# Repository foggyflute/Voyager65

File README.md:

# V65LE
Low-cost 65% keyboard PCB

[Supported Layouts](http://www.keyboard-layout-editor.com/#/gists/98784f0271c0b4e29edec77185eb883a)

## Features
* Atxmega32a4u controller for Keyplus firmware usage
* Overcurrent and ESD protection, along with physically durable design
* Type-C USB connector
* Easy programming via TC2030-IDC header
* Alps and MX compatibility
* **Completely** open-source: All the files you need to make a keyboard with it, design a case/plate for it, or even produce a batch of PCBs for your next GB, are all to be available free.
* Low-cost with LED circuitry removed. Recommended for Alps-only boards.

## Status
* Main Voyager65 switch matrix confirmed functional.
	* V65AE shares its matrix circuitry and pinout with Voyager65.
* Prototypes yet to be created.

## Variants
* [Voyager65](https://github.com/ai03-2725/Voyager65): The main variant of the Voyager65 family. All the cutting edge features.
* V65LE: This branch. Low-cost variant.
* [V65AE](https://github.com/ai03-2725/Voyager65/tree/V65AE): Alps-specific variant.

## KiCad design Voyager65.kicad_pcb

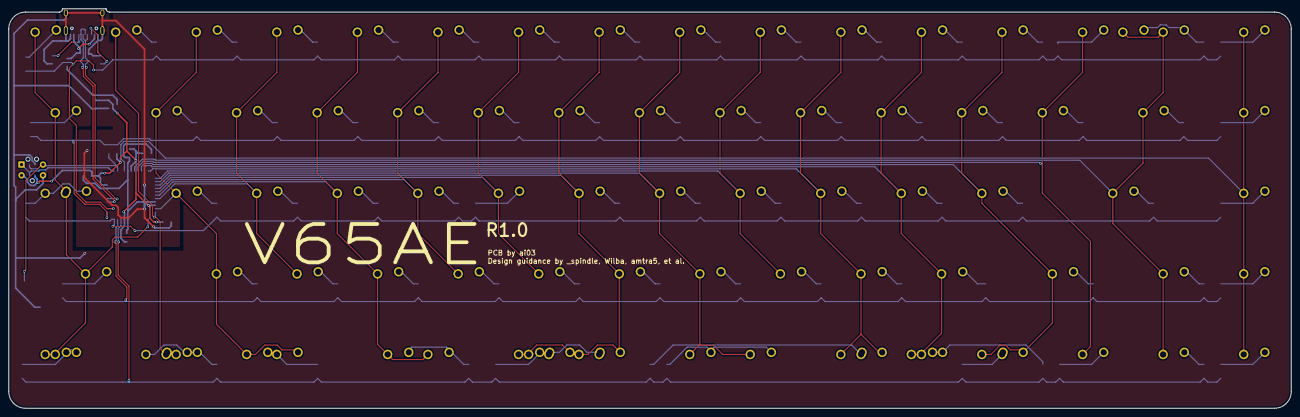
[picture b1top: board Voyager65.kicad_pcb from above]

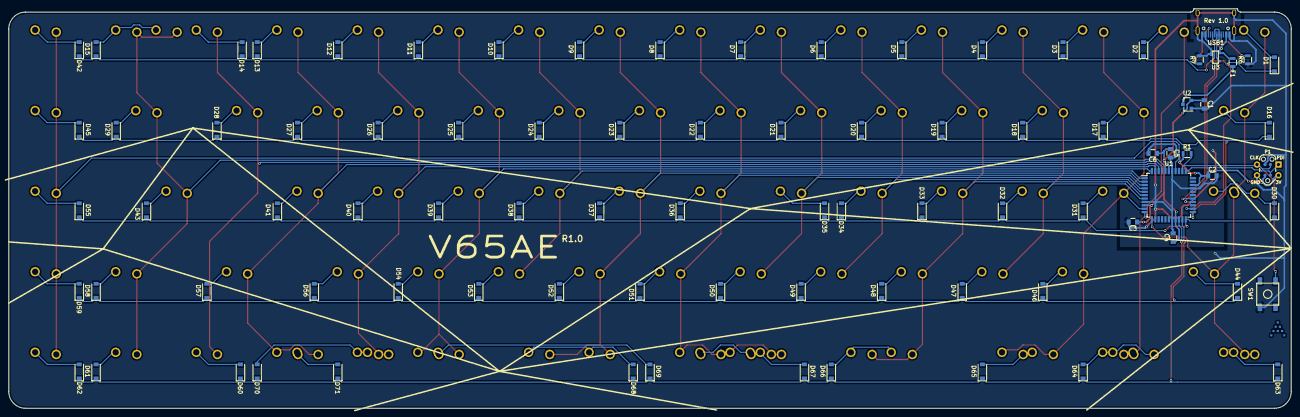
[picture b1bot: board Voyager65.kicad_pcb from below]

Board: 2 copper layers, 303.2 x 94.5 mm, 173 parts (87 on the bottom side), 102 nets.

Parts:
C1: 1u; C_0805
C2, C3, C4, C5: 0.1u; C_0805
C6: 10u; C_0805
D1, D2, D3, D4, D5, D6, D7, D8, D9, D10, D11, D12, D13, D14, D15, D16, D17, D18, D19, D20, D21, D22, D23, D24, D25, D26, D27, D28, D29, D30, D31, D32, D33, D34, D35, D36, D37, D38, D39, D40, D41, D42, D43, D44, D45, D46, D47, D48, D49, D50, D51, D52, D53, D54, D55, D56, D57, D58, D59, D60, D61, D62, D63, D64, D65, D66, D67, D68, D69, D70, D71: D_Small; D_SOD-123
F1: 500mA; R_0805
K_#0_1, K_#1, K_#2, K_#3, K_#4, K_#5, K_#6, K_#7, K_#8, K_#9: MX-1U; ALPS-1U
K_'1: MX-1U; ALPS-1U
K_,1: MX-1U; ALPS-1U
K_-1: MX-1U; ALPS-1U
K_.1: MX-1U; ALPS-1U
K_/1: MX-1U; ALPS-1U
K_;1: MX-1U; ALPS-1U
K_=1: MX-1U; ALPS-1U
K_A1: MX-1U; ALPS-1U
K_B1: MX-1U; ALPS-1U
K_BACK1: MX-2U; ALPS-2U
K_BACK2: MX-1U; ALPS-1U
K_C1: MX-1U; ALPS-1U
K_CAPS1: MX-1.75U; ALPS-1.75U
K_CAPS2: MX-1.25U; ALPS-1.25U
K_D1: MX-1U; ALPS-1U
K_DEL1: MX-1U; ALPS-1U
K_DOWN1: MX-1U; ALPS-1U
K_E1: MX-1U; ALPS-1U
K_ENTER1: MX-2.25U; ALPS-2.25U
K_ESC1: MX-1U; ALPS-1U
K_EX1, K_EX2, K_EX3, K_EX4: MX-1U; ALPS-1U
K_F1: MX-1U; ALPS-1U
K_G1: MX-1U; ALPS-1U
K_H1: MX-1U; ALPS-1U
K_I1: MX-1U; ALPS-1U
K_J1: MX-1U; ALPS-1U
K_K1: MX-1U; ALPS-1U
K_L1: MX-1U; ALPS-1U
K_LEFT1: MX-1U; ALPS-1U
K_LM1, K_LM3, K_LM7: MX-1.5U; ALPS-1.5U
K_LM2, K_LM4, K_LM5, K_LM6: MX-1.25U; ALPS-1.25U
K_M1: MX-1U; ALPS-1U
K_N1: MX-1U; ALPS-1U
K_O1: MX-1U; ALPS-1U
K_P1: MX-1U; ALPS-1U
K_Q1: MX-1U; ALPS-1U
K_R1: MX-1U; ALPS-1U
K_RIGHT1: MX-1U; ALPS-1U
K_RM1, K_RM4, K_RM6: MX-1U; ALPS-1U
K_RM2, K_RM5: MX-1.5U; ALPS-1.5U
K_RM3: MX-1.25U; ALPS-1.25U
K_S1: MX-1U; ALPS-1U
K_SHIFT1: MX-2.25U; ALPS-2.25U
K_SHIFT2: MX-1.75U; ALPS-1.75U
K_T1: MX-1U; ALPS-1U
K_TAB1: MX-1.5U; ALPS-1.5U
K_U1: MX-1U; ALPS-1U
K_UP1: MX-1U; ALPS-1U
K_V1: MX-1U; ALPS-1U
K_W1: MX-1U; ALPS-1U
K_X1: MX-1U; ALPS-1U
K_Y1: MX-1U; ALPS-1U
K_Z1: MX-1U; ALPS-1U
K_[1: MX-1U; ALPS-1U
K_\1: MX-1.5U; ALPS-1.5U
K_]1: MX-1U; ALPS-1U
P1: TC2030-IDC; TC2030-NL_SMALL_AND_IDC_PDI
R1: 10k; R_0805
R6, R7: 5.1k; R_0805
SP1, SP7: MX-2.25U; ALPS-2.25U
SP2: MX-7U; ALPS-1U
SP3: MX-6.25U; ALPS-1U
SP4: MX-1.25U; ALPS-1.25U
SP5, SP9: MX-2.75U; ALPS-2.75U
SP6: MX-6.5U; ALPS-6.5U
SP8: MX-1.5U; ALPS-1.5U
SW1: SW_PUSH; SKQG-1155865
U1: ATXMEGA32A4U-AU; TQFP-44_10x10mm_Pitch0.8mm
U2: MCP1700T-3002E/TT; SOT-23
U3: PRTR5V0U2X; SOT143B
USB1: HRO-TYPE-C-31-M-12

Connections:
+3V3: C1.1, C2.1, C3.1, C4.1, C5.1, C6.1, P1.2, R1.1, U1.9, U1.19, U1.31, U1.39, U2.2
+5V: F1.1, U2.3
COL0: K_CAPS1.1, K_CAPS2.2, K_ESC1.1, K_LM1.1, K_LM2.1, K_SHIFT1.1, K_TAB1.1, U1.12
COL1: K_#1.1, K_LM3.1, K_LM4.2, K_LM5.1, U1.11
COL2: K_#2.1, K_A1.1, K_LM6.1, K_LM7.2, K_Q1.1, K_Z1.1, U1.10
COL3: K_#3.1, K_S1.1, K_W1.1, K_X1.1, U1.7
COL4: K_#4.1, K_C1.1, K_D1.1, K_E1.1, SP1.1, SP7.1, U1.6
COL5: K_#5.1, K_F1.1, K_R1.1, K_V1.1, U1.5
COL6: K_#6.1, K_B1.1, K_G1.1, K_T1.1, U1.4
COL7: K_#7.1, K_H1.1, K_N1.1, K_Y1.1, SP2.1, SP3.2, SP4.1, SP6.2, SP8.1, U1.3
COL8: K_#8.1, K_J1.1, K_M1.1, K_U1.1, SP5.1, SP9.1, U1.2
COL9: K_#9.1, K_,1.1, K_I1.1, K_K1.1, U1.1
COL10: K_#0_1.1, K_.1.1, K_L1.1, K_O1.1, K_RM1.1, K_RM2.2, U1.44
COL11: K_-1.1, K_/1.1, K_;1.1, K_P1.1, K_RM3.1, K_RM4.1, U1.43
COL12: K_'1.1, K_=1.1, K_RM5.1, K_RM6.2, K_SHIFT2.1, K_[1.1, U1.42
COL13: K_DEL1.1, K_LEFT1.1, K_]1.1, U1.41
COL14: K_BACK1.1, K_BACK2.1, K_DOWN1.1, K_ENTER1.1, K_UP1.1, K_\1.1, U1.40
COL15: K_EX1.1, K_EX2.1, K_EX3.1, K_EX4.1, K_RIGHT1.1, U1.37
D+: U1.27, U3.2, USB1.6, USB1.8
D-: U1.26, U3.3, USB1.5, USB1.7
GND: C1.2, C2.2, C3.2, C4.2, C5.2, C6.2, P1.6, R6.1, R7.2, SW1.1, U1.8, U1.18, U1.30, U1.38, U2.1, U3.1, USB1.1, USB1.12, USB1.13
unnamed: D1.2, K_ESC1.2
unnamed: D2.2, K_#1.2
unnamed: D3.2, K_#2.2
unnamed: D4.2, K_#3.2
unnamed: D5.2, K_#4.2
unnamed: D6.2, K_#5.2
unnamed: D7.2, K_#6.2
unnamed: D8.2, K_#7.2
unnamed: D9.2, K_#8.2
unnamed: D10.2, K_#9.2
unnamed: D11.2, K_#0_1.2
unnamed: D12.2, K_-1.2
unnamed: D13.2, K_=1.2
unnamed: D14.2, K_DEL1.2
unnamed: D15.2, K_BACK1.2, K_BACK2.2
unnamed: D16.2, K_TAB1.2
unnamed: D17.2, K_Q1.2
unnamed: D18.2, K_W1.2
unnamed: D19.2, K_E1.2
unnamed: D20.2, K_R1.2
unnamed: D21.2, K_T1.2
unnamed: D22.2, K_Y1.2
unnamed: D23.2, K_U1.2
unnamed: D24.2, K_I1.2
unnamed: D25.2, K_O1.2
unnamed: D26.2, K_P1.2
unnamed: D27.2, K_[1.2
unnamed: D28.2, K_]1.2
unnamed: D29.2, K_\1.2
unnamed: D30.2, K_CAPS1.2, K_CAPS2.1
unnamed: D31.2, K_A1.2
unnamed: D32.2, K_S1.2
unnamed: D33.2, K_D1.2
unnamed: D34.2, K_F1.2
unnamed: D35.2, K_G1.2
unnamed: D36.2, K_H1.2
unnamed: D37.2, K_J1.2
unnamed: D38.2, K_K1.2
unnamed: D39.2, K_L1.2
unnamed: D40.2, K_;1.2
unnamed: D41.2, K_'1.2
unnamed: D42.2, K_EX1.2
unnamed: D43.2, K_ENTER1.2
unnamed: D44.2, K_SHIFT1.2
unnamed: D45.2, K_EX2.2
unnamed: D46.2, K_Z1.2
unnamed: D47.2, K_X1.2
unnamed: D48.2, K_C1.2
unnamed: D49.2, K_V1.2
unnamed: D50.2, K_B1.2
unnamed: D51.2, K_N1.2
unnamed: D52.2, K_M1.2
unnamed: D53.2, K_,1.2
unnamed: D54.2, K_.1.2
unnamed: D55.2, K_EX3.2
unnamed: D56.2, K_/1.2
unnamed: D57.2, K_SHIFT2.2
unnamed: D58.2, K_UP1.2
unnamed: D59.2, K_EX4.2
unnamed: D60.2, K_LEFT1.2
unnamed: D61.2, K_DOWN1.2
unnamed: D62.2, K_RIGHT1.2
unnamed: D63.2, K_LM1.2, K_LM2.2
unnamed: D64.2, K_LM3.2, K_LM4.1, K_LM5.2
unnamed: D65.2, K_LM6.2, K_LM7.1
unnamed: D66.2, SP1.2, SP7.2
unnamed: D67.2, SP2.2, SP3.1, SP4.2, SP6.1, SP8.2
unnamed: D68.2, SP5.2, SP9.2
unnamed: D69.2, K_RM1.2, K_RM2.1
unnamed: D70.2, K_RM3.2, K_RM4.2
unnamed: D71.2, K_RM5.2, K_RM6.1
unnamed: R6.2, USB1.4
unnamed: R7.1, USB1.10
PDI: P1.1, U1.34
PDI_CLK: P1.5, R1.2, SW1.2, U1.35
ROW0: D1.1, D2.1, D3.1, D4.1, D5.1, D6.1, D7.1, D8.1, D9.1, D10.1, D11.1, D12.1, D13.1, D14.1, D15.1, D42.1, U1.24
ROW1: D16.1, D17.1, D18.1, D19.1, D20.1, D21.1, D22.1, D23.1, D24.1, D25.1, D26.1, D27.1, D28.1, D29.1, D45.1, U1.23
ROW2: D30.1, D31.1, D32.1, D33.1, D34.1, D35.1, D36.1, D37.1, D38.1, D39.1, D40.1, D41.1, D43.1, D55.1, U1.22
ROW3: D44.1, D46.1, D47.1, D48.1, D49.1, D50.1, D51.1, D52.1, D53.1, D54.1, D56.1, D57.1, D58.1, D59.1, U1.21
ROW4: D60.1, D61.1, D62.1, D63.1, D64.1, D65.1, D66.1, D67.1, D68.1, D69.1, D70.1, D71.1, U1.20
VCC: F1.2, U3.4, USB1.2, USB1.11

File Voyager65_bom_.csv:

Component,Description,Part,References,Value,Footprint,Quantity Per PCB,Datasheet
1,Unpolarized capacitor,C_Small,C2 C3 C4 C5,0.1u,C_0603,4,
2,Unpolarized capacitor,C_Small,C6,10u,C_0603,1,
3,Unpolarized capacitor,C_Small,C1,1u,C_0603,1,
4,"Diode, small symbol",D_Small,D1 D2 D3 D4 D5 D6 D7 D8 D9 D10 D11 D12 D13 D14 D15 D16 D17 D18 D19 D20 D21 D22 D23 D24 D25 D26 D27 D28 D29 D30 D31 D32 D33 D34 D35 D36 D37 D38 D39 D40 D41 D42 D43 D44 D45 D46 D47 D48 D49 D50 D51 D52 D53 D54 D55 D56 D57 D58 D59 D60 D61 D62 D63 D64 D65 D66 D67 D68 D69 D70 D71,D_Small,D_SOD-123,71,
5,"resettable fuse, polymeric positive temperature coefficient (PPTC), small symbol",Polyfuse_Small,F1,500mA,R_0805,1,
6,,TC2030-IDC,P1,TC2030-IDC,TC2030-NL_SMALL_AND_IDC_PDI,1,
7,"Resistor, small symbol",R_Small,R1,10k,R_0603,1,
8,"Resistor, small symbol",R_Small,R6 R7,5.1k,R_0603,2,
9,,SW_PUSH,SW1,SW_PUSH,SKQG-1155865,1,
10,"TQFP44, 16k Flash, 4k Boot, 2k SRAM, 1k EEPROM, JTAG, USB",ATXMEGA32A4U-AU,U1,ATXMEGA32A4U-AU,TQFP-44_10x10mm_Pitch0.8mm,1,http://www.atmel.com/Images/Atmel-8387-8-and16-bit-AVR-Micro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
11,"250mA Low Quiscent Current LDO, 3.0V output, SOT-23",MCP1700-3002E_SOT23,U2,MCP1700T-3002E/TT,SOT-23,1,http://ww1.microchip.com/downloads/en/DeviceDoc/20001826C.pdf
12,,PRTR5V0U2X,U3,PRTR5V0U2X,SOT143B,1,
13,,HRO-TYPE-C-31-M-12,USB1,HRO-TYPE-C-31-M-12,HRO-TYPE-C-31-M-12,1,https://datasheet.lcsc.com/szlcsc/TYPE-C-31-M-12-Female-head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





Component Groups:,13
Component Count:,87
Fitted Components:,87
Number of PCBs:,1
Total components:,87
Schematic Version:,
Schematic Date:,
BoM Date:,6/8/2018 1:08:43 AM
Schematic Source:,C:/Users/Ryota/Documents/GitHub/Voyager65/Voyager65.sch
KiCad Version:,Eeschema 4.0.7

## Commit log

2018-01-19 :lollipop: Added .gitattributes & .gitignore files
2018-01-19 Add submodules
2018-01-19 Generate project
2018-01-19 Remove submodule
2018-01-19 Add missing submodule
2018-01-19 Begin building schematic, bit by bit
2018-01-19 Voltage tests
2018-01-19 Continue schematic
2018-01-19 Add libs
2018-01-20 Tune up controller to final state
2018-01-20 Implement ESD protection
2018-01-20 Bind controller footprints
2018-01-20 Generate preliminary netlist
2018-01-20 Change PCB sheet size
2018-01-20 Place 60% footprint
2018-01-20 Sort parts on PCB
2018-01-20 Roughly break out controller
2018-01-21 Place down some matrix stuff
2018-01-21 Create IS31FL3731-SALS2 schem module
2018-01-21 Wire the LED controller
2018-01-21 Add LED matrix labels
2018-01-21 Label row 1 of switches
2018-01-21 Continue labeling and adding keys on matrix
2018-01-22 Build right shift in separate sheet
2018-01-22 Break matrix up into multiple sheets
2018-01-22 Finish labeling key names
2018-01-22 Assign footprints, along with placeholders for mx
2018-01-22 Repair footprints on main matrix sheet
2018-01-22 Repair all mx footprints
2018-01-22 Start placing some footprints
2018-01-22 Fix backspace, finish row 1
2018-01-22 Dislodge PTC for routing
2018-01-22 Place some modifiers
2018-01-22 Layout broken out bottom row
2018-01-22 Fix right shift sizes
2018-01-22 Combine and place right shift cluster
2018-01-22 Combine and position bottom row
2018-01-22 Swap alps row for alps-only fp
2018-01-22 Layout 2nd row
2018-01-22 Layout all keys
2018-01-22 Fix USB net name
2018-01-22 Route USB
2018-01-22 Unroute USB
2018-01-22 Break out controller a bit
2018-01-22 Breakout controller further
2018-01-22 Update breakout for RGB placement
2018-01-22 Remove alps row
2018-01-22 Repair bottom row after refractor]
2018-01-22 Recombine bottom row
2018-01-22 Add RGB
2018-01-22 Position RGBs
2018-01-22 Fix LED MCU breakout
2018-01-22 Wire PDI header
2018-01-22 Rename I2C net for easier routing
2018-01-22 I2C routing
2018-01-22 Preliminary MCU routing
2018-01-22 Wire cols 0-5
2018-01-22 Close for tonight
2018-01-23 Route bus upwards
2018-01-23 Label cols
2018-01-23 Connect cols
2018-01-23 Forgot one col, fix
2018-01-23 Wire and name rows
2018-01-23 Place diodes, remove duplicates
2018-01-23 Place RGB caps
2018-01-23 Begin connecting diodes to switches
2018-01-23 Connect up more diodes
2018-01-23 Fix incorrect spacebar pinout
2018-01-23 Route a few RGBs
2018-01-23 Add 500 ohm resistor inline to RGB data
2018-01-23 Place RGB resistor
2018-01-23 Reorder col pins
2018-01-24 Connect most cols
2018-01-24 Add basic row col to subsheets
2018-01-25 Begin fixing rshift pinout
2018-01-25 Fully pinout rshift
2018-01-25 Pinout right mods
2018-01-25 Wire more compat footprints
2018-01-25 Continue routing
2018-01-25 Fill controller gnd plane
2018-01-25 Continue routing without LED
2018-01-25 Route all except controller 5v rail
2018-01-25 Tune trace busses to take less space
2018-01-26 Begin routing LED rows
2018-01-28 Route left half LED rows
2018-01-28 Temporary progress save, end of branch for now
2018-01-28 Unroute LEDs
2018-01-28 Unroute and reposition PCB
2018-01-28 Swap footprints for No-LED counterparts
2018-01-28 Begin creating LED matrix
2018-01-28 Place and annotate LED schematic components
2018-01-28 Wire lefthand matrix schematic
2018-01-28 Join '\' key and ISO '~' key together to save diode
2018-01-28 Wire righthand matrix
2018-01-28 Update submodule
2018-01-28 Assign footprints
2018-01-28 Place some of the LED footprints
2018-01-28 Prepare for adding more footprints
2018-01-28 Add submodules again
2018-01-28 Add lefthand compat LEDs
2018-01-28 Update submods
2018-01-28 Load and position extra LEDs for lefthand
2018-01-28 Fix LED quantity for enter
2018-01-28 Place righthand LED footprints
2018-01-28 Add missing shift-row footprints
2018-01-28 Finish placing LEDs
2018-01-28 Nudge some parts around
2018-01-28 Route lefthand LED matrix
2018-01-28 Wire the rows
2018-01-28 Wire LED matrix
2018-01-28 Route LEDs
2018-01-28 Tune up LED tracks
2018-01-28 Begin routing switch matrix
2018-01-28 Route cols
2018-01-28 Route two rows
2018-01-28 Route most of matrix
2018-01-28 Connect all cols
2018-01-28 Progress save
2018-01-29 Connect all
    Hooray!
2018-01-29 Add logic schem module
2018-01-29 Place ground planes
2018-01-29 Flow more gnd plane, fix i2c voltage
2018-01-29 Fill gnd
2018-01-29 Read netlist
2018-01-29 Fix RGB voltage
2018-01-29 Finalize
2018-01-29 Generate Gerbers
2018-01-29 Finished
2018-01-29 Tune up some more traces
2018-01-29 Add in missing backspace stabs
2018-01-29 Fix traces to match stabilizer holes
2018-01-29 Replace PTC fuse for 0805
2018-01-29 Replace PTC footprint on PCB
2018-01-29 Swap ESD protection chip
2018-01-30 Assign ESD protection chip footprint
2018-01-30 Replace and reroute ESD chip
2018-01-30 Improve USB isolation
2018-01-30 Improve USB isolation further
2018-01-30 Update VCC-5V flow
2018-01-30 Update gerber
2018-01-30 Move silkscreen labels to legible locations
2018-01-30 Update some routing\
2018-01-30 Tune routing further
2018-01-30 Add some silkscreen art
2018-01-30 Add credits
2018-01-30 Redo gnd planes, add via fence near controller
2018-01-30 Finish silkscreen and decorations
2018-01-30 Add some stuff to silkscreen
2018-01-30 Add revision text and create final gerbers
2018-01-30 Render images
2018-01-30 Add image to readme
2018-02-05 Update right mods
2018-02-05 Change and update leftmods
2018-02-05 Update spacebar
2018-02-05 Assign footprints to updated mods
2018-02-05 Breakout and place switches
2018-02-05 Add LEDs
2018-02-05 Place LEDs and move out diodes
2018-02-06 Move row into place
2018-02-06 Route leftmods and spacebar
2018-02-06 Route RM1, right mod leds
2018-02-06 Finish routing
2018-02-09 Move USB setup
2018-02-09 Add component libraries
2018-02-09 Replace USB connector
2018-02-09 Route USB C
2018-02-09 Fill and tune Gnd Plane
2018-02-10 Protrude USB position by 0.5mm
2018-02-10 Change line layers on footprint
2018-02-10 Replace outline, rereoute some controller traces
2018-02-10 Optimize traces
2018-02-10 Optimize traces further
2018-02-10 Label pads on programming header
2018-02-10 Clean remaining traces
2018-02-10 Tune USB breakout
2018-02-10 Remove ISO
2018-02-10 Remove traces from removed switches
2018-02-10 Remove LEDs for removed switches on schematic
2018-02-10 Remove LEDs on PCB and reroute
2018-02-10 Tune some more traces
2018-02-10 Temporary finish route optimizing
2018-02-10 Adjust line weight for deco
2018-02-10 Tune component labels
    Horizontal for system, vertical for matrix
2018-02-10 Add logo
2018-02-10 Finalize PCB, DRC checks
2018-02-10 Update gerbers
2018-02-10 Update renders
2018-02-11 Fix readme
2018-02-14 Begin adding wireless support
2018-02-15 Tune up some traces
2018-02-15 Temporary progress save
2018-03-05 Unroute, prepare for LED chip replacement
2018-03-05 Create LICENSE
2018-03-05 never mind
2018-03-05 Experiment around
2018-03-05 Revert wireless functionality
    Not this time.
2018-03-05 Re-verify
2018-03-06 Swap LED controller for IS31FL3733
2018-03-06 Update netlist
2018-03-06 Lock some footprints
2018-03-06 Halt the project
2018-03-06 Fuck it 0603
    Rip soldering
2018-03-06 Revert LED structure
2018-03-06 Wire LED rows
2018-03-06 Begin routing
2018-03-06 Temporary save before rollback
2018-03-06 Replace and route bus
2018-03-06 Fix spacebar LED
2018-03-06 Finalize for error checking
2018-03-07 Improve routing
2018-03-07 Temporary save during trace cleanup
2018-03-07 Update fill and logo text
2018-04-01 Tune up routing
2018-04-05 Tune routing
2018-04-05 Tune silk
2018-04-05 New renders
2018-04-05 Remove empty sheet
2018-04-07 Push the bus 5mil
2018-04-07 Finalize routing and add gerbers
2018-04-07 New gerbers
2018-04-09 Final check for production
2018-04-10 Finalize 60% branch
2018-04-10 Begin conversion from Voyager to 65 variant
2018-04-10 Temporarily update readme
2018-04-10 Clean up some files
2018-04-11 Replace MCU, route bus
2018-04-11 A few more traces before I sleep
2018-04-11 Sleep
2018-04-11 Remove LED MCU
2018-04-11 Remove MCU
2018-04-12 Finish project basic routing
2018-04-12 Tune zones
2018-04-12 Start adding mounts
2018-04-12 Update submodules again
2018-04-12 Add mounts
2018-04-12 Add button footprint
2018-04-12 Replace reset switch
2018-04-12 Nudge some traces
2018-04-12 Remove tiny trace remains
2018-04-12 Seems like master branch is still on old submod version
2018-04-12 New render
2018-04-12 Nudge readme
2018-04-12 Tune top plate
2018-04-12 Generate first set of gerbers
2018-04-14 Modernize Type C footprints
2018-04-14 Prepare gerbers for production
2018-04-18 Tune USB connector
2018-04-18 Tune 5V trace
2018-04-18 Begin fleshing out BOM
2018-04-18 Finalize BOM
2018-04-18 Redo gerbers
2018-04-18 Gerber attempt 2
2018-04-18 New gerbers again
2018-04-18 Tune more traces
2018-04-18 TADA68 mounting holes
2018-04-18 Tada conversion complete
2018-04-18 TADA68 alu chassis compatibility conversion
2018-04-19 Generate plate, tune routing
2018-04-19 Very final error check and regen of gerbers
2018-04-19 Tune silkscreen
2018-04-19 Create plate files with dummy drill files
    Because fab complains
2018-04-19 Swap USB back
2018-04-19 Generate MX plates
2018-04-20 Tweak plate
2018-04-20 Final tune-up
2018-04-20 Final tuning before production
2018-05-19 Final touches
2018-05-19 Remove IS31FL3733
2018-05-19 Begin unrouting
2018-05-27 Progress
2018-05-27 Low cost edition complete
2018-05-27 Update info for V65LE
2018-05-27 Remove URL from readme
2018-05-29 Alps Edition is here
2018-05-29 Reroute + make easier to solder
2018-05-29 Revision 1.1
    Clean routing
2018-05-29 Repair readme
2018-05-29 Push readme
2018-06-26 Tune for Lunar use
